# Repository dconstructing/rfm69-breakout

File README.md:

Breakout Board for the HopeRF RFM69 modules

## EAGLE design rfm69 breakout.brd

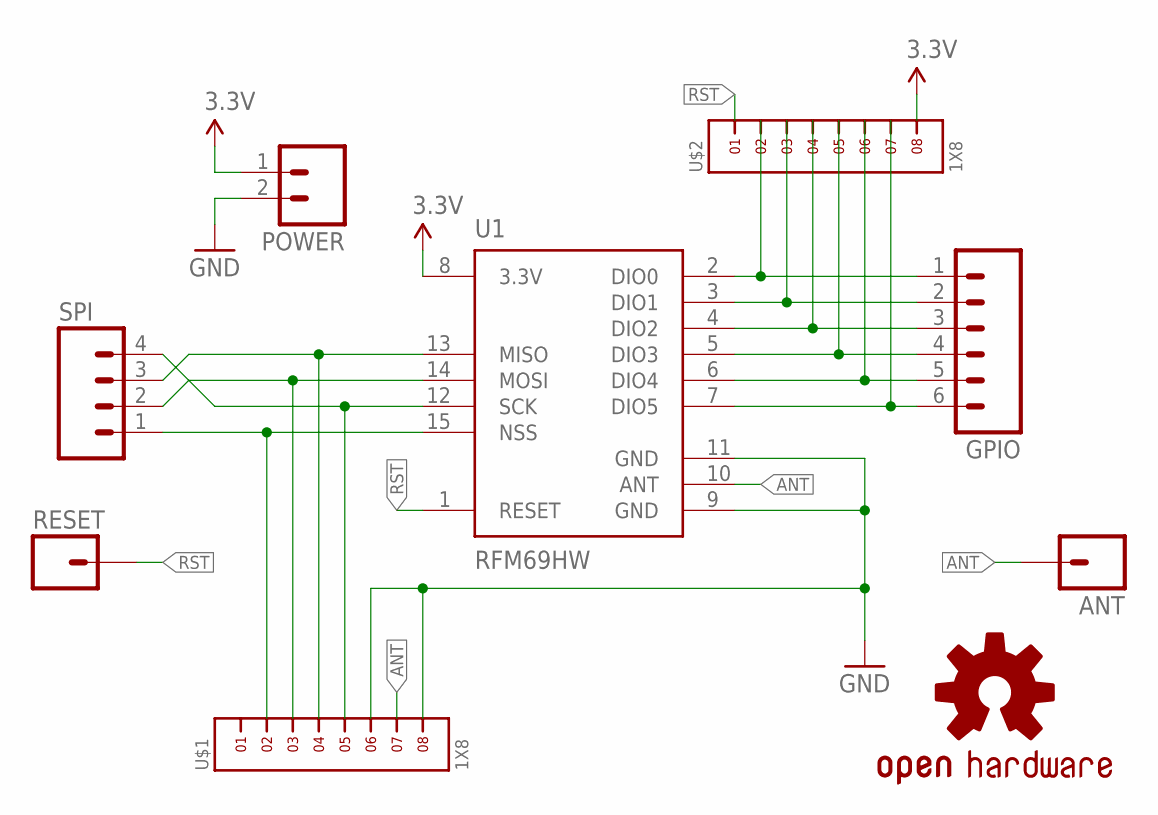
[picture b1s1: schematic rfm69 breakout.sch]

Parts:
ANT: M01PTH; 1X01
GPIO: M06SILK_FEMALE_PTH; 1X06
LOGO1: OSHW-LOGOL; OSHW-LOGO-L
POWER: M02PTH; 1X02
RESET: M01PTH; 1X01
SPI: M04PTH; 1X04
U1: RFM69HW; RFM69W-XXXS2
U$1, U$2: 1X8

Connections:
3.3V: POWER.1, U1.8 (3.3V), U$2.8
ANT: ANT.1, U1.10 (ANT), U$1.7
GND: POWER.2, U1.9 (GND), U1.11 (GND), U$1.6, U$1.8
unnamed: GPIO.1, U1.2 (DIO0), U$2.2
unnamed: GPIO.2, U1.3 (DIO1), U$2.3
unnamed: GPIO.3, U1.4 (DIO2), U$2.4
unnamed: GPIO.4, U1.5 (DIO3), U$2.5
unnamed: GPIO.5, U1.6 (DIO4), U$2.6
unnamed: GPIO.6, U1.7 (DIO5), U$2.7
unnamed: SPI.1, U1.15 (NSS), U$1.2
unnamed: SPI.2, U1.14 (MOSI), U$1.3
unnamed: SPI.3, U1.13 (MISO), U$1.4
unnamed: SPI.4, U1.12 (SCK), U$1.5
RST: RESET.1, U1.1 (RESET), U$2.1

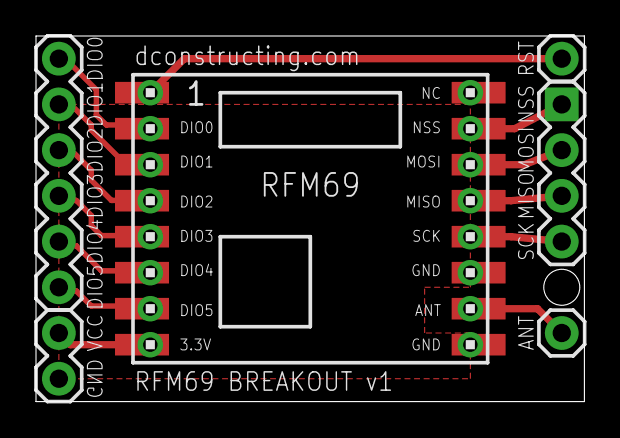
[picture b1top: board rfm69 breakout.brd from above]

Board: 2 copper layers, 30.5 x 20.3 mm, 9 parts (1 on the bottom side), 14 nets.

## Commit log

2016-04-20 First draft version of breakout board
2016-04-20 Labels and smaller ground plane
2016-04-20 Ignore lock files
2016-04-21 Bottom screens and smaller ground plane
2016-04-22 Label receiving pins/pads for RFM69 module

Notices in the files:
parts and their libraries:
SparkFun-Connectors: Licensing: Creative Commons ShareAlike 4.0 International - https://creativecommons.org/licenses/by-sa/4.0
